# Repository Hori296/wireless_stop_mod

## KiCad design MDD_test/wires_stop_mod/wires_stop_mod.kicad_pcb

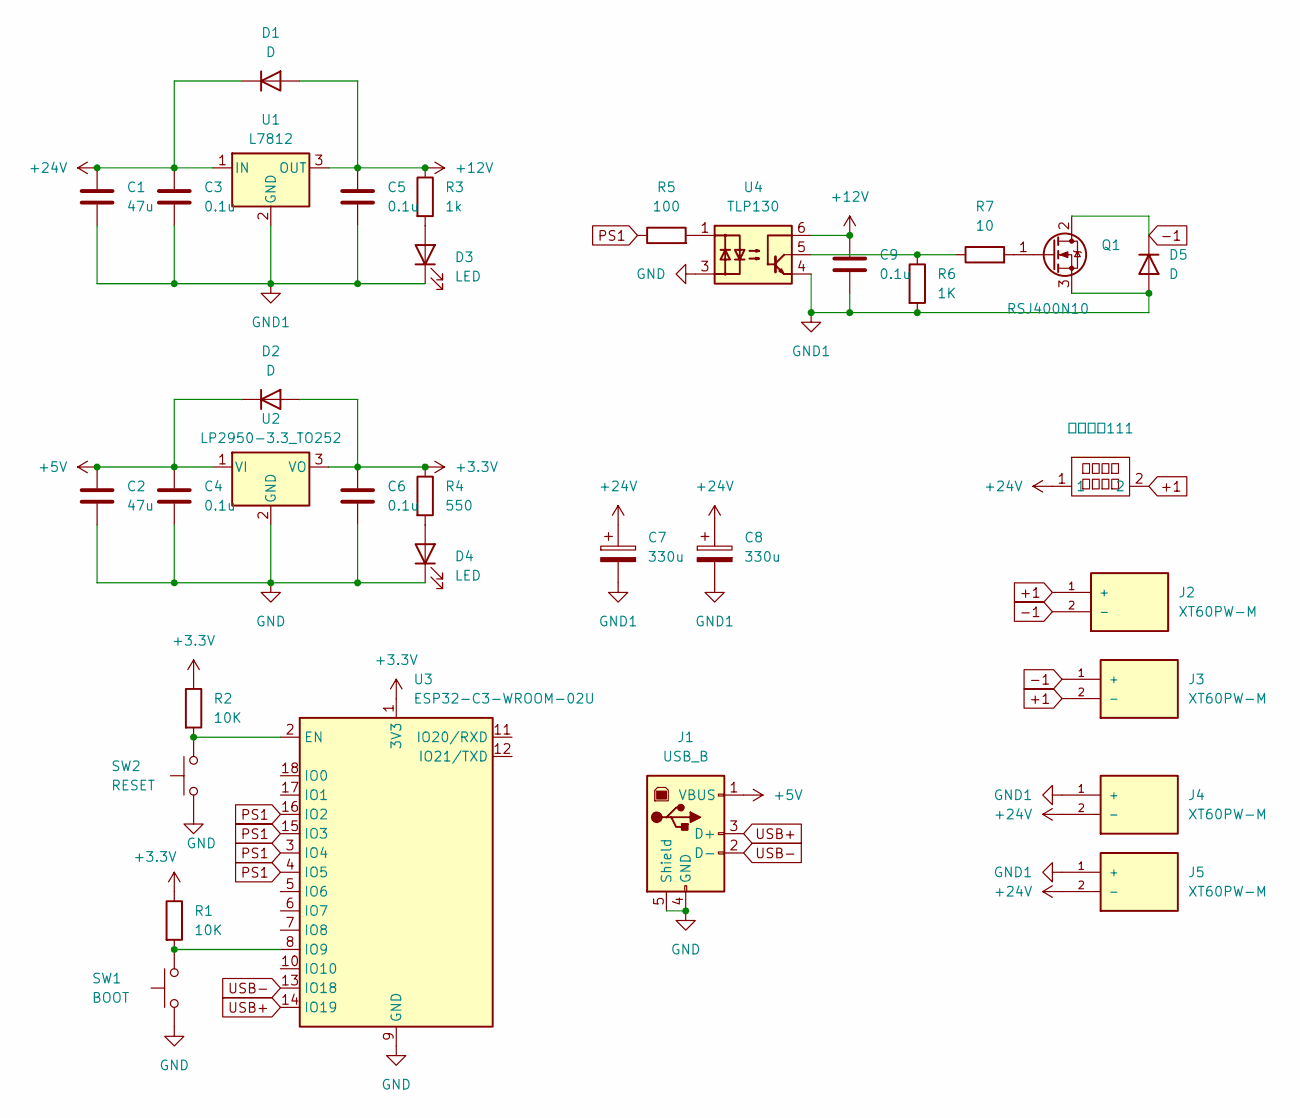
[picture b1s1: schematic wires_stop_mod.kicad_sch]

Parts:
C1, C2: 47u; C_0603_1608Metric
C3, C4, C5, C6, C9: 0.1u; C_0603_1608Metric
C7, C8: 330u; CP_Elec_10x10
D1, D2, D5: D; D_SOD-128
D3, D4: LED; LED_0603_1608Metric
J1: USB_B; USB_B_Lumberg_2411_02_Horizontal
J2: XT60PW-M; AMASS_XT60PW-F_1x02_P7.20mm_Horizontal; PARTREV V1.2
J3, J5: XT60PW-M; AMASS_XT30PW-F_1x02_P2.50mm_Horizontal; PARTREV V1.2
J4: XT60PW-M; AMASS_XT60PW-M_1x02_P7.20mm_Horizontal; PARTREV V1.2
Q1: RSJ400N10; TO-263-2
R1, R2: 10K; C_0603_1608Metric
R3: 1k; C_0603_1608Metric
R4: 550; C_0603_1608Metric
R5: 100; C_0603_1608Metric
R6: 1K; C_0603_1608Metric
R7: 10; C_0603_1608Metric
SW1: BOOT; SW_PUSH-12mm
SW2: RESET; SW_PUSH-12mm
U1: L7812; TO-252-2
U2: LP2950-3.3_TO252; TO-252-2
U3: ESP32-C3-WROOM-02U
U4: TLP130; MFSOP6-5_4.4x3.6mm_P1.27mm
ヒューズ111: XS-506A

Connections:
+1: J2.1 (+), J3.2 (-), ヒューズ111.2
+3.3V: C6.1, D2.2 (A), R1.1, R2.1, R4.1, U2.3 (VO), U3.1 (3V3); also elsewhere on the board
+5V: C2.1, C4.1, D2.1 (K), J1.1 (VBUS), U2.1 (VI)
+12V: C5.1, C9.1, D1.2 (A), R3.1, U1.3 (OUT), U4.6
+24V: C1.1, C3.1, C7.1, C8.1, D1.1 (K), J4.2 (-), J5.2 (-), U1.1 (IN), ヒューズ111.1
-1: D5.1 (K), J2.2 (-), J3.1 (+), Q1.2 (D)
GND: C2.2, C4.2, C6.2, D4.1 (K), J1.4 (GND), J1.5 (Shield), SW1.1, SW2.1, U2.2 (GND), U3.9 (GND), U3.19 (GND), U4.3; also elsewhere on the board
GND1: C1.2, C3.2, C5.2, C7.2, C8.2, C9.2, D3.1 (K), D5.2 (A), J4.1 (+), J5.1 (+), Q1.3 (S), R6.2, U1.2 (GND), U4.4
unnamed: D3.2 (A), R3.2
unnamed: D4.2 (A), R4.2
unnamed: Q1.1 (G), R7.2
unnamed: R5.2, U4.1
unnamed: R6.1, R7.1, U4.5
unnamed 13: R2.2, SW2.2, U3.2 (EN); also elsewhere on the board
unnamed 14: R1.2, SW1.2, U3.8 (IO9); also elsewhere on the board
PS1: R5.1, U3.3 (IO4), U3.4 (IO5), U3.15 (IO3), U3.16 (IO2); also elsewhere on the board
USB+: J1.3 (D+), U3.14 (IO19); also elsewhere on the board
USB-: J1.2 (D-), U3.13 (IO18); also elsewhere on the board

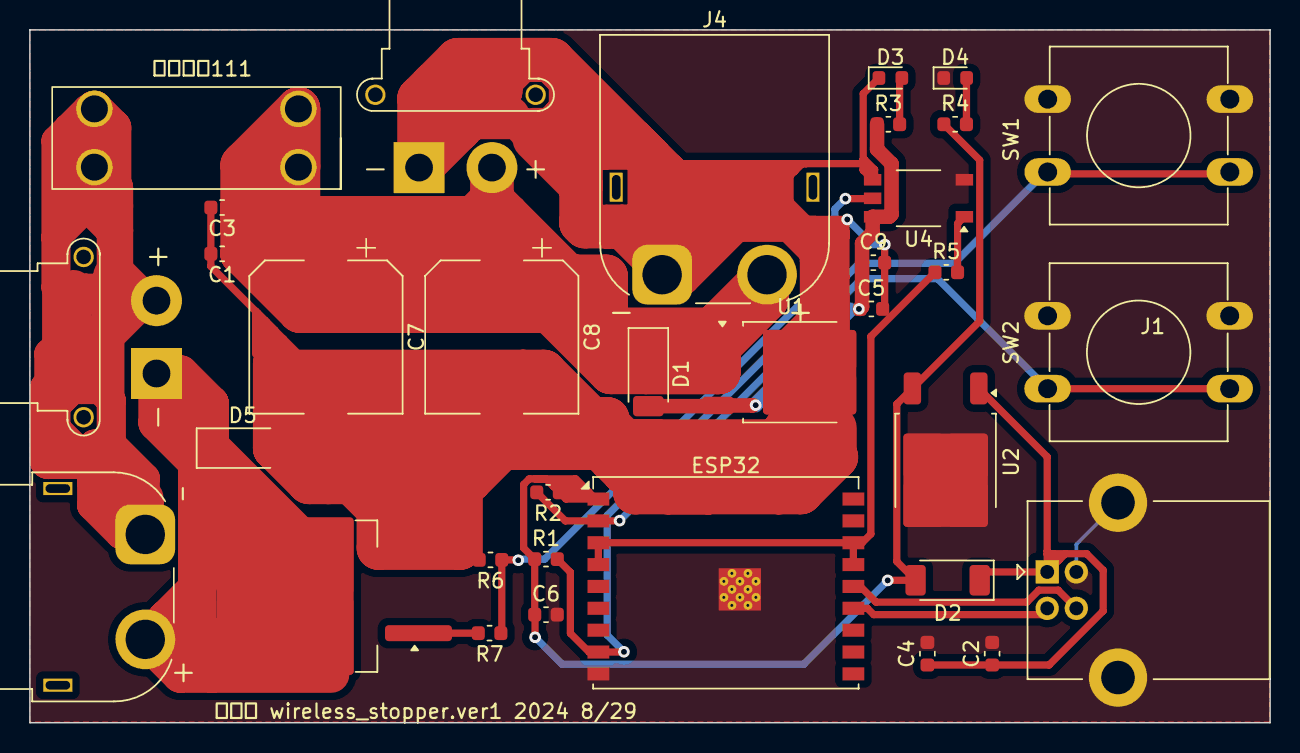
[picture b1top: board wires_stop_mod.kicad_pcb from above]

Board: 2 copper layers, 85.1 x 47.5 mm, 34 parts (0 on the bottom side), 18 nets.

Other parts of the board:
ESP32: ESP32-C3-WROOM-02U

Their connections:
+3.3V: ESP32.1 (3V3); also elsewhere on the board
GND: ESP32.9 (GND), ESP32.19 (GND); also elsewhere on the board
unnamed 13: ESP32.2 (EN); also elsewhere on the board
unnamed 14: ESP32.8 (IO9); also elsewhere on the board
PS1: ESP32.3 (IO4), ESP32.4 (IO5), ESP32.15 (IO3), ESP32.16 (IO2); also elsewhere on the board
USB+: ESP32.14 (IO19); also elsewhere on the board
USB-: ESP32.13 (IO18); also elsewhere on the board

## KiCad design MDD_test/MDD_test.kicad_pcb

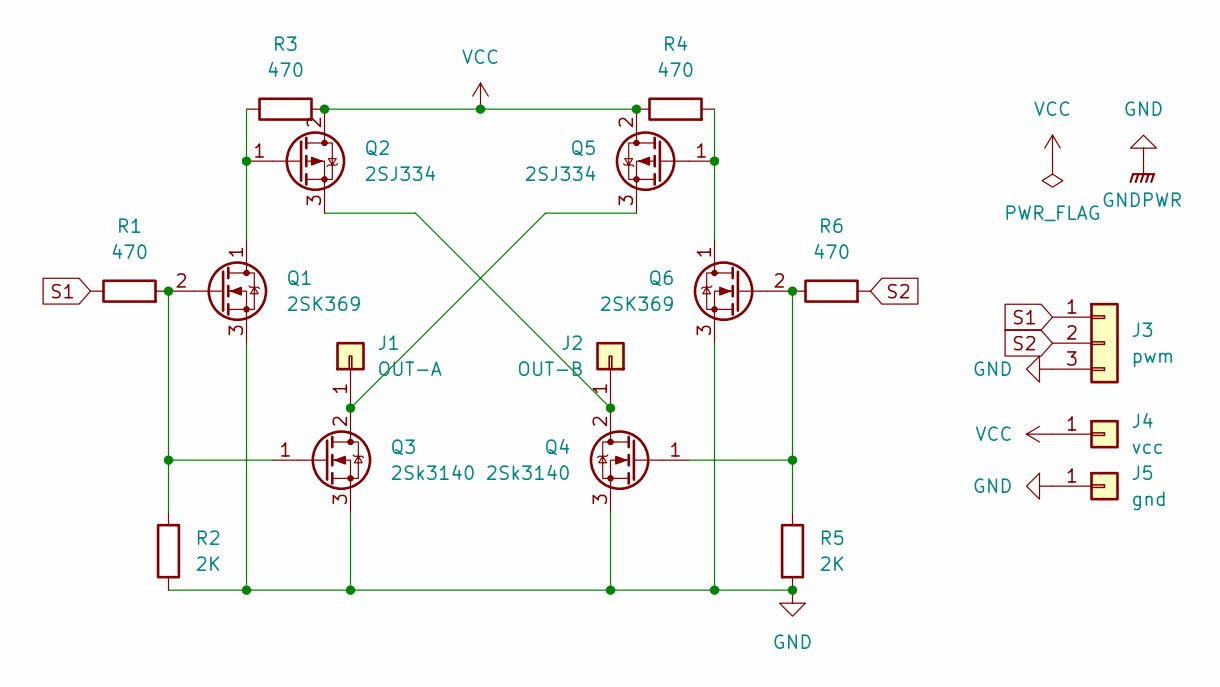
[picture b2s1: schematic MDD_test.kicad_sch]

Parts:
J1: OUT-A; TestPoint_THTPad_D3.0mm_Drill1.5mm
J2: OUT-B; TestPoint_THTPad_D3.0mm_Drill1.5mm
J3: pwm; PinHeader_1x03_P2.54mm_Vertical
J4: vcc; TestPoint_THTPad_D3.0mm_Drill1.5mm
J5: gnd; TestPoint_THTPad_D3.0mm_Drill1.5mm
Q1, Q6: 2SK369; TO-92
Q2, Q5: 2SJ334; TO-220-3_Vertical
Q3, Q4: 2Sk3140; TO-220-3_Vertical
R1, R3, R4, R6: 470; R_Axial_DIN0207_L6.3mm_D2.5mm_P10.16mm_Horizontal
R2, R5: 2K; R_Axial_DIN0207_L6.3mm_D2.5mm_P10.16mm_Horizontal

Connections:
GND: J3.3, J5.1, Q1.3 (S), Q3.3 (S), Q4.3 (S), Q6.3 (S), R2.1, R5.2
unnamed: J1.1, Q3.2 (D), Q5.3 (S)
unnamed: J2.1, Q2.3 (S), Q4.2 (D)
unnamed: Q1.1 (D), Q2.1 (G), R3.1
unnamed: Q1.2 (G), Q3.1 (G), R1.2, R2.2
unnamed: Q4.1 (G), Q6.2 (G), R5.1, R6.1
unnamed: Q5.1 (G), Q6.1 (D), R4.2
S1: J3.1, R1.1
S2: J3.2, R6.2
VCC: J4.1, Q2.2 (D), Q5.2 (D), R3.2, R4.1

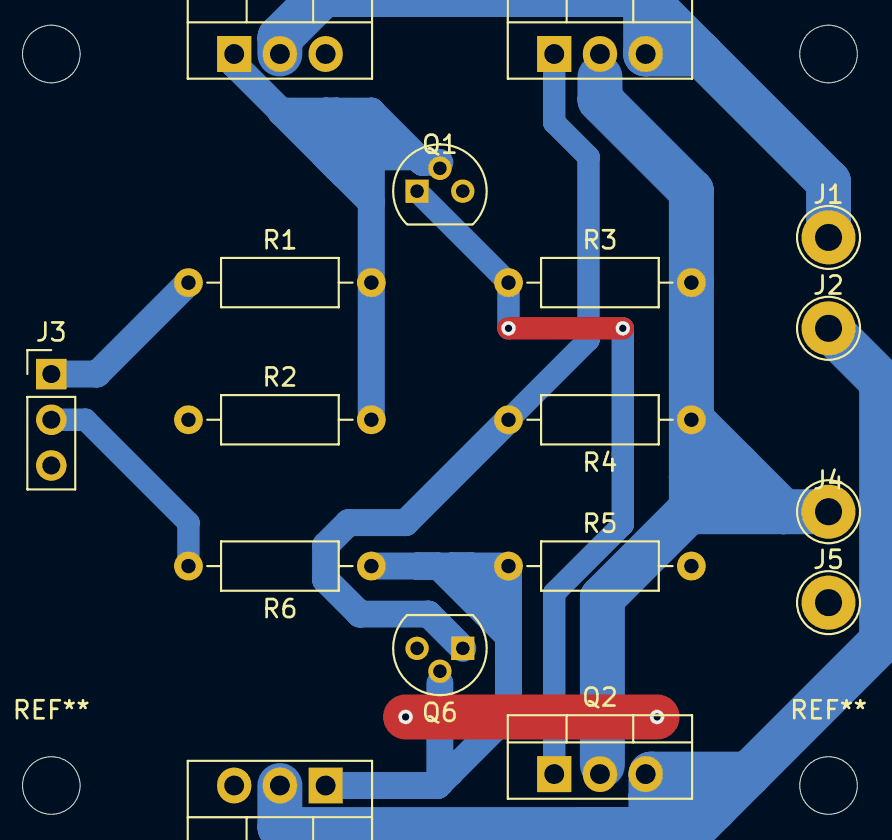
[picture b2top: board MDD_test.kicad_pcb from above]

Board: 2 copper layers, 17 parts (0 on the bottom side), 10 nets.
